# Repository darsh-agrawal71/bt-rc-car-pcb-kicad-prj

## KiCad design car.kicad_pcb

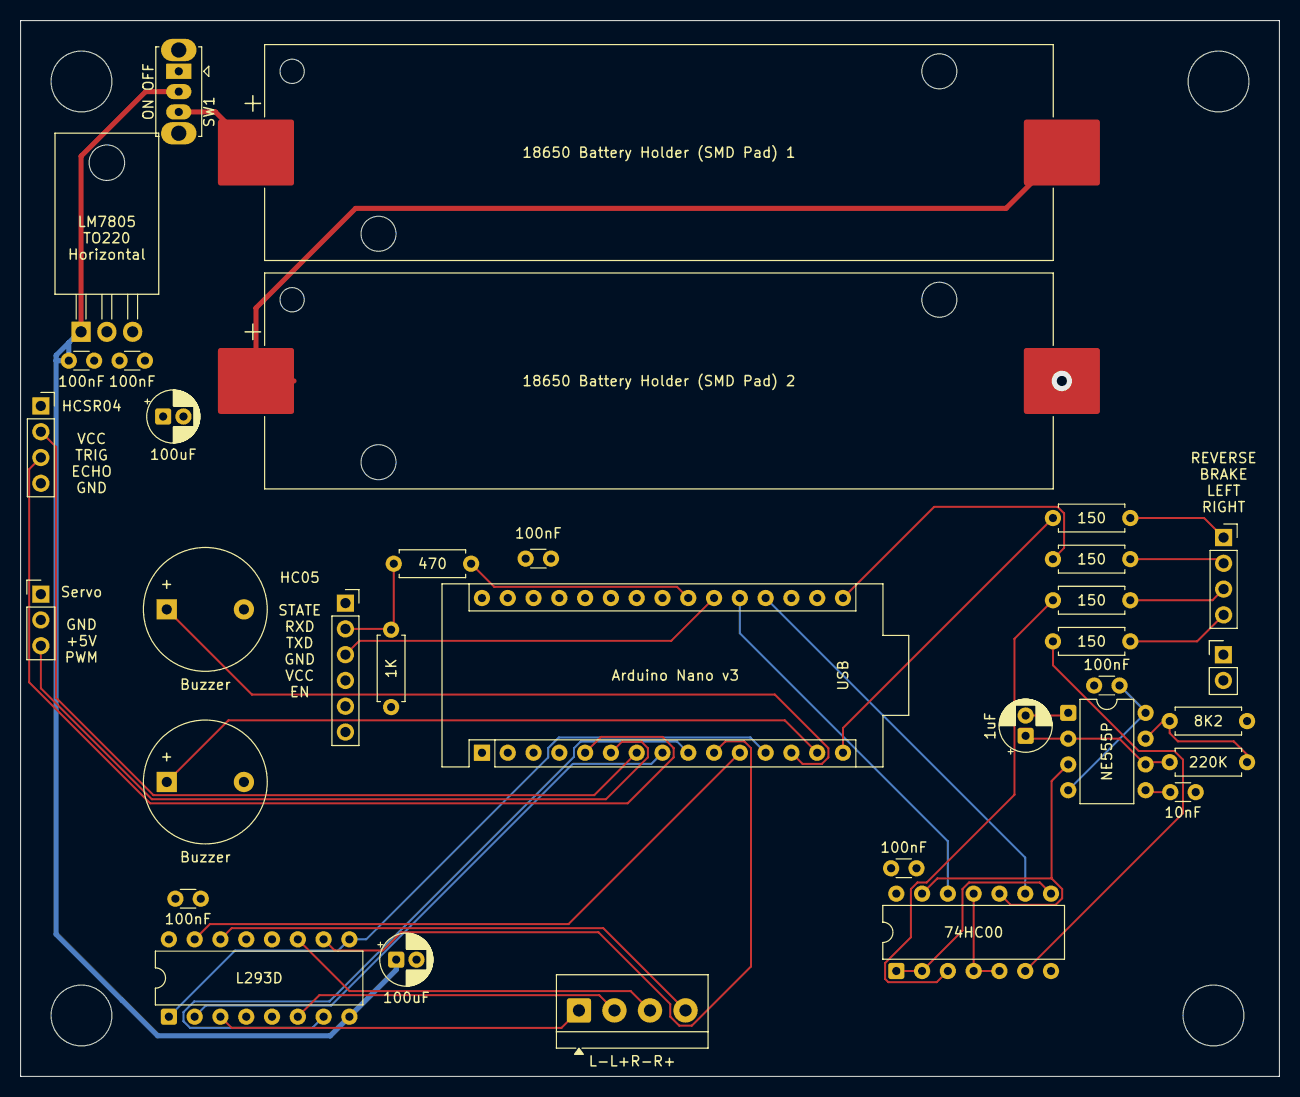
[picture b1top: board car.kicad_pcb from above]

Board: 4 copper layers, 124.0 x 104.0 mm, 34 parts (0 on the bottom side), 38 nets.

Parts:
A1: Arduino Nano v3; Arduino_Nano
BT1, BT2: Battery_Cell; BatteryHolder_Keystone_1042_1x18650
BZ1, BZ2: Buzzer; Buzzer_12x9.5RM7.6
C1: 10nF; C_Disc_D3.0mm_W1.6mm_P2.50mm
C2: 1uF; CP_Radial_D5.0mm_P2.00mm
C3, C13: 100uF; CP_Radial_D5.0mm_P2.00mm
C5, C7, C8, C9, C10, C12: 100nF; C_Disc_D3.0mm_W1.6mm_P2.50mm
J1: GND GND; PinHeader_1x02_P2.54mm_Vertical
J2: L-L+R-R+; TerminalBlock_4Ucon_1x04_P3.50mm_Horizontal
J3: HCSR04 VCC TRIG ECHO GND; PinSocket_1x04_P2.54mm_Vertical
J4: HC05 STATE RXD TXD GND VCC EN; PinSocket_1x06_P2.54mm_Vertical
LED1: REVERSE BRAKE LEFT RIGHT; PinSocket_1x04_P2.54mm_Vertical
R1: 1K; R_Axial_DIN0207_L6.3mm_D2.5mm_P7.62mm_Horizontal
R2: 470; R_Axial_DIN0207_L6.3mm_D2.5mm_P7.62mm_Horizontal
R3: 8K2; R_Axial_DIN0207_L6.3mm_D2.5mm_P7.62mm_Horizontal
R4: 220K; R_Axial_DIN0207_L6.3mm_D2.5mm_P7.62mm_Horizontal
R5, R6, R7, R8: 150; R_Axial_DIN0207_L6.3mm_D2.5mm_P7.62mm_Horizontal
SRV1: Servo GND +5V PWM; PinHeader_1x03_P2.54mm_Vertical
SW1: ON OFF; SW_Slide_SPDT_Straight_CK_OS102011MS2Q
U1: LM7805 TO220 Horizontal; TO-220-3_Horizontal_TabDown
U2: L293D; DIP-16_W7.62mm
U3: NE555P; DIP-8_W7.62mm
U4: 74HC00; DIP-14_W7.62mm

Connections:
+5V: A1.27 (+5V), C7.1, C8.1, C9.1, C10.1, C12.1, C13.1, J3.4, J4.5, R3.2, SRV1.2, U1.3 (VO), U2.16 (VCC1), U3.4 (R), U3.8 (VCC), U4.14 (VCC)
+BATT: C3.1, C5.1, SW1.2 (B), U1.1 (VI), U2.8 (VCC2)
/555_OUT: U3.3 (Q), U4.10, U4.13
/ALARM_GPIO_PWM: A1.14 (D11), BZ2.1 (+)
/BRAKE_GPIO: A1.16 (D13), R6.1
/ECHO_GPIO: A1.7 (D4), J3.2
/HORN_GPIO_PWM: A1.13 (D10), BZ1.1 (+)
/L+_GPIO: A1.10 (D7), U2.10 (3A)
/L+_OUT: J2.3, U2.11 (3Y)
/L-_GPIO: A1.11 (D8), U2.15 (4A)
/L-_OUT: J2.4, U2.14 (4Y)
/R+_GPIO: A1.8 (D5), U2.2 (1A)
/R+_OUT: J2.1, U2.3 (1Y)
/R-_GPIO: A1.9 (D6), U2.7 (2A)
/R-_OUT: J2.2, U2.6 (2Y)
/REVERSE_GPIO: A1.15 (D12), R5.1
/RX_GPIO: A1.21 (A2), J4.3
/SERVO_GPIO_PWM: A1.6 (D3), SRV1.3
/SPEED_GPIO_PWM: A1.12 (D9), U2.1 (EN1,2), U2.9 (EN3,4)
/TLEFT_GPIO: A1.19 (A0), U4.9
/TRIGHT_GPIO: A1.20 (A1), U4.12
/TRIG_GPIO: A1.5 (D2), J3.3
/TX: J4.2, R1.1, R2.1
/TX_GPIO: A1.22 (A3), R2.2
GND: A1.4 (GND), A1.29 (GND), BT2.2 (-), BZ1.2 (-), BZ2.2 (-), C1.1, C2.2, C3.2, C5.2, C7.2, C8.2, C9.2, C10.2, C12.2, C13.2, J1.1, J1.2, J3.1, J4.4, R1.2, SRV1.1, U1.2 (GND), U2.4 (GND), U2.5 (GND), U2.12 (GND), U2.13 (GND), U3.1 (GND), U4.7 (GND)
unnamed: BT1.1 (+), SW1.3 (C)
unnamed: BT1.2 (-), BT2.1 (+)
unnamed: LED1.1, R5.2
unnamed: LED1.2, R6.2
unnamed: LED1.3, R7.2
unnamed: LED1.4, R8.2
unnamed: R7.1, U4.3
unnamed: R8.1, U4.6
unnamed: C1.2, U3.5 (CV)
unnamed: R3.1, R4.2, U3.7 (DIS)
unnamed: C2.1, R4.1, U3.2 (TR), U3.6 (THR)
unnamed: U4.1, U4.2, U4.8
unnamed: U4.4, U4.5, U4.11

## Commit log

2025-08-13 rev2
